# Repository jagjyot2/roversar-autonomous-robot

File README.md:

# RoverSAR — Autonomous Search & Rescue Ground Robot

**RoverSAR** is an autonomous differential-drive search-and-rescue (SAR) ground robot combining modular **PlatformIO ESP32 C++ firmware**, a **FastAPI + WebSocket 2D physics/SLAM simulator**, a **responsive React + TypeScript dark-mode control HUD**, **3D-printable OpenSCAD/STL chassis CAD**, **KiCad 8 schematics & BOM**, and a **BenchTwin** hardware staging package.

---

## Key Capabilities

- **Modular ESP32 Firmware (`firmware/`)**:
  - `motor_control/`: Differential-drive inverse/forward kinematics, `50 Hz` anti-windup wheel encoder PID, `20 kHz` TB6612FNG / L298N PWM driver.
  - `sensors/`: 5-channel `VL53L0X` ToF array (`XSHUT` address reassignment `0x30..0x34`), `MPU6050` IMU yaw/tilt fusion, `IRAM_ATTR` quadrature encoder odometry (`1440 CPR`), ADC1 2S Li-Ion battery monitor.
  - `navigation/`: 2D Bayesian log-odds occupancy grid mapper + VFH+ local reactive obstacle avoidance + waypoint pursuit.
  - `safety/`: Deterministic **500 ms comm-loss heartbeat watchdog** (immediate motor halt), IMU `> 35°` rollover cutoff, critical battery cutoff (`<= 6.0 V`), and latched software/hardware NC E-STOP.
  - `communication/` & `camera/`: Built-in RFC-6455 WebSocket + HTTP JSON server and ESP32-CAM MJPEG stream link.
- **2D Physics Simulator & Responsive Control HUD (`simulator/` + `dashboard/`)**:
  - Real-time `50 Hz` differential-drive dynamics, ToF laser raycasting against indoor SAR rooms/debris, live occupancy grid SLAM, and synthetic raycasted FPV ESP32-CAM JPEG/MJPEG stream.
  - Dark-mode React + TypeScript HUD served directly at `/` featuring a **touch virtual joystick + WASD**, **live 2D occupancy map & laser rays canvas**, **click-to-set-waypoint**, **FPV camera HUD**, **RPM/battery/watchdog gauges**, **E-STOP**, and **"Simulate Comm Loss (500ms Test)"** fault injection.
- **Mechanical CAD, KiCad & BenchTwin (`cad/`, `hardware/`, `benchtwin/`)**:
  - `240 × 180 × 95 mm` PETG chassis deck (`roversar_base_plate.stl`), 5-beam ToF sensor arc (`vl53l0x_sensor_mount.stl`), and 15° ESP32-CAM tilt bracket (`esp32_cam_tilt_bracket.stl`).
  - Complete KiCad 8 schematic, netlist, `BOM.csv`, mechanical/CG analysis, GPIO wiring map, and BenchTwin staging package.

---

## Quick Start

### 1. Run Simulator & Web Control HUD
```bash
pip install -r requirements.txt
uvicorn simulator.rover_sim_server:app --host 0.0.0.0 --port 8050
```
Open **`http://localhost:8050`** on desktop or mobile:
- Use **WASD / Arrow keys** or the **virtual touch joystick** to drive manually.
- **Click/tap anywhere** inside the 2D arena map to dispatch an autonomous VFH+ waypoint.
- Click **"Simulate Comm Loss (500ms Test)"** to verify the watchdog trips `COMM_LOSS_500MS` and halts both motors within 500 ms.
- Click **EMERGENCY E-STOP** to immediately lock drive actuation.

### 2. Run Automated Verification Tests
```bash
pytest -v
```

### 3. Build ESP32 Firmware (`firmware/`) & Run Wokwi Simulation (`wokwi/`)
```bash
cd firmware
pio run
```
Once built, `wokwi/wokwi.toml` points directly to `firmware/.pio/build/esp32dev/firmware.bin` and `firmware.elf`.
- **VS Code Wokwi Extension**: Open `wokwi/diagram.json` and run **Wokwi: Start Simulator**.
- **Wokwi CLI**: Set `WOKWI_CLI_TOKEN` and run `wokwi-cli` inside `wokwi/` (see [`wokwi/README.md`](./wokwi/README.md)).
- **Supported vs. Stubbed Components**: `ESP32-WROOM-32D`, `MPU6050`, `HC-SR04`, `NC E-STOP`, `2S VBAT divider`, and PWM/fault LEDs are natively modeled in Wokwi; the 5-ch `VL53L0X` array, `TB6612FNG` + 1440 CPR quadrature encoders, and `ESP32-CAM` use custom Wokwi chip stubs paired with the 50 Hz Python physics harness (see [`simulation/documentation/COMPONENT-SUPPORT-MATRIX.md`](./simulation/documentation/COMPONENT-SUPPORT-MATRIX.md)).

### 4. Rebuild React + TypeScript Dashboard (`dashboard/`)
```bash
cd dashboard
npm install
npm run build
```

---

## Repository Structure
- `firmware/` — Modular PlatformIO ESP32 C++ project (`include/`, `src/`, `platformio.ini`)
- `simulator/` — FastAPI + WebSocket `/ws/rover` physics, raycasting, SLAM, VFH+, and safety engine
- `dashboard/` — React + TypeScript + Vite responsive dark-mode ground control UI (`dist/` served at `/`)
- `cad/` — OpenSCAD `.scad` sources, reproducible STL builder, and binary `.stl` meshes
- `hardware/` — `CHASSIS-DESIGN.md`, `WIRING-DIAGRAM.md`, `roversar.kicad_sch`, `roversar.net`, `BOM.csv`
- `simulation/` — Simulator-independent HAL (`adapters/common/`), active `wokwi/` adapter, preserved `benchtwin/` manifest, fault/navigation `scenarios/`, and `COMPONENT-SUPPORT-MATRIX.md`
- `wokwi/` — Active Wokwi ESP32 diagram (`diagram.json`), `wokwi.toml`, and custom chip stubs (`chip-quad-encoder`, `chip-vl53l0x-array`)
- `benchtwin/` — Preserved BenchTwin hardware-in-the-loop staging package (`roversar.btw`, manifest, netlist, BOM, STL) for future reactivation
- `tests/` — Automated pytest suite covering kinematics, PID, odometry/mapping, wall avoidance, 500 ms failsafe, FastAPI/WS, STL, KiCad & BenchTwin validation
- `docs/ARCHITECTURE.md` & `ROADMAP.md` — System architecture & future engineering roadmap

---

## License
Released under the [MIT License](./LICENSE).

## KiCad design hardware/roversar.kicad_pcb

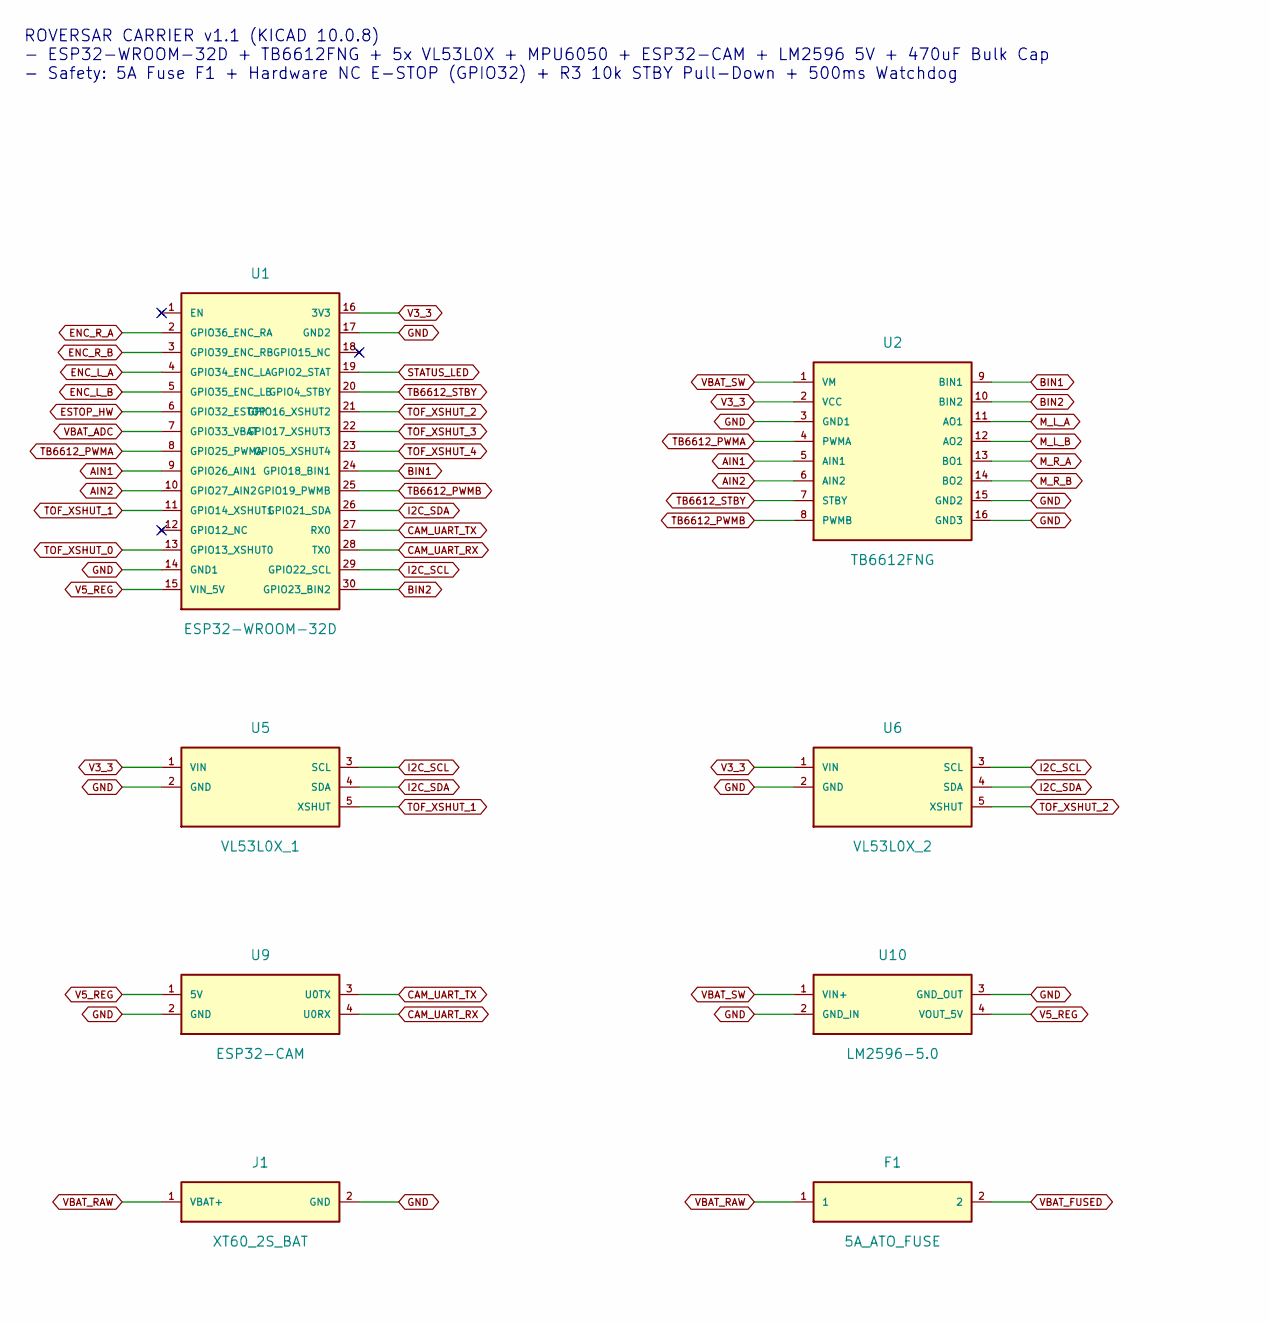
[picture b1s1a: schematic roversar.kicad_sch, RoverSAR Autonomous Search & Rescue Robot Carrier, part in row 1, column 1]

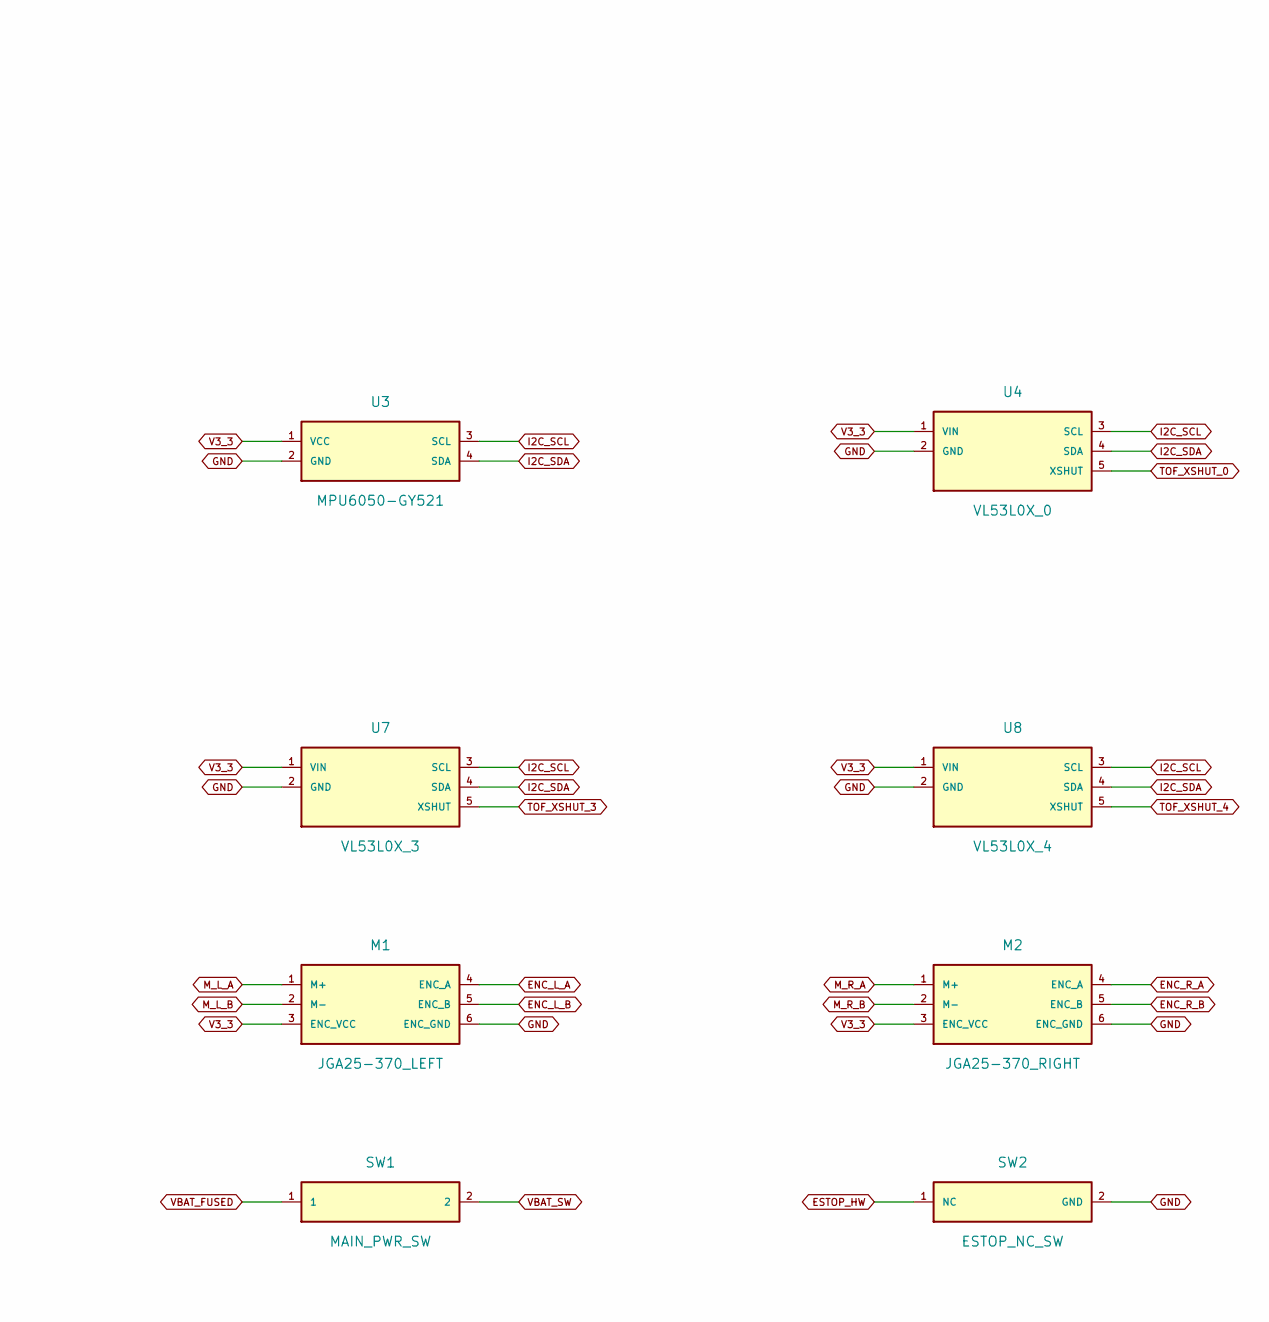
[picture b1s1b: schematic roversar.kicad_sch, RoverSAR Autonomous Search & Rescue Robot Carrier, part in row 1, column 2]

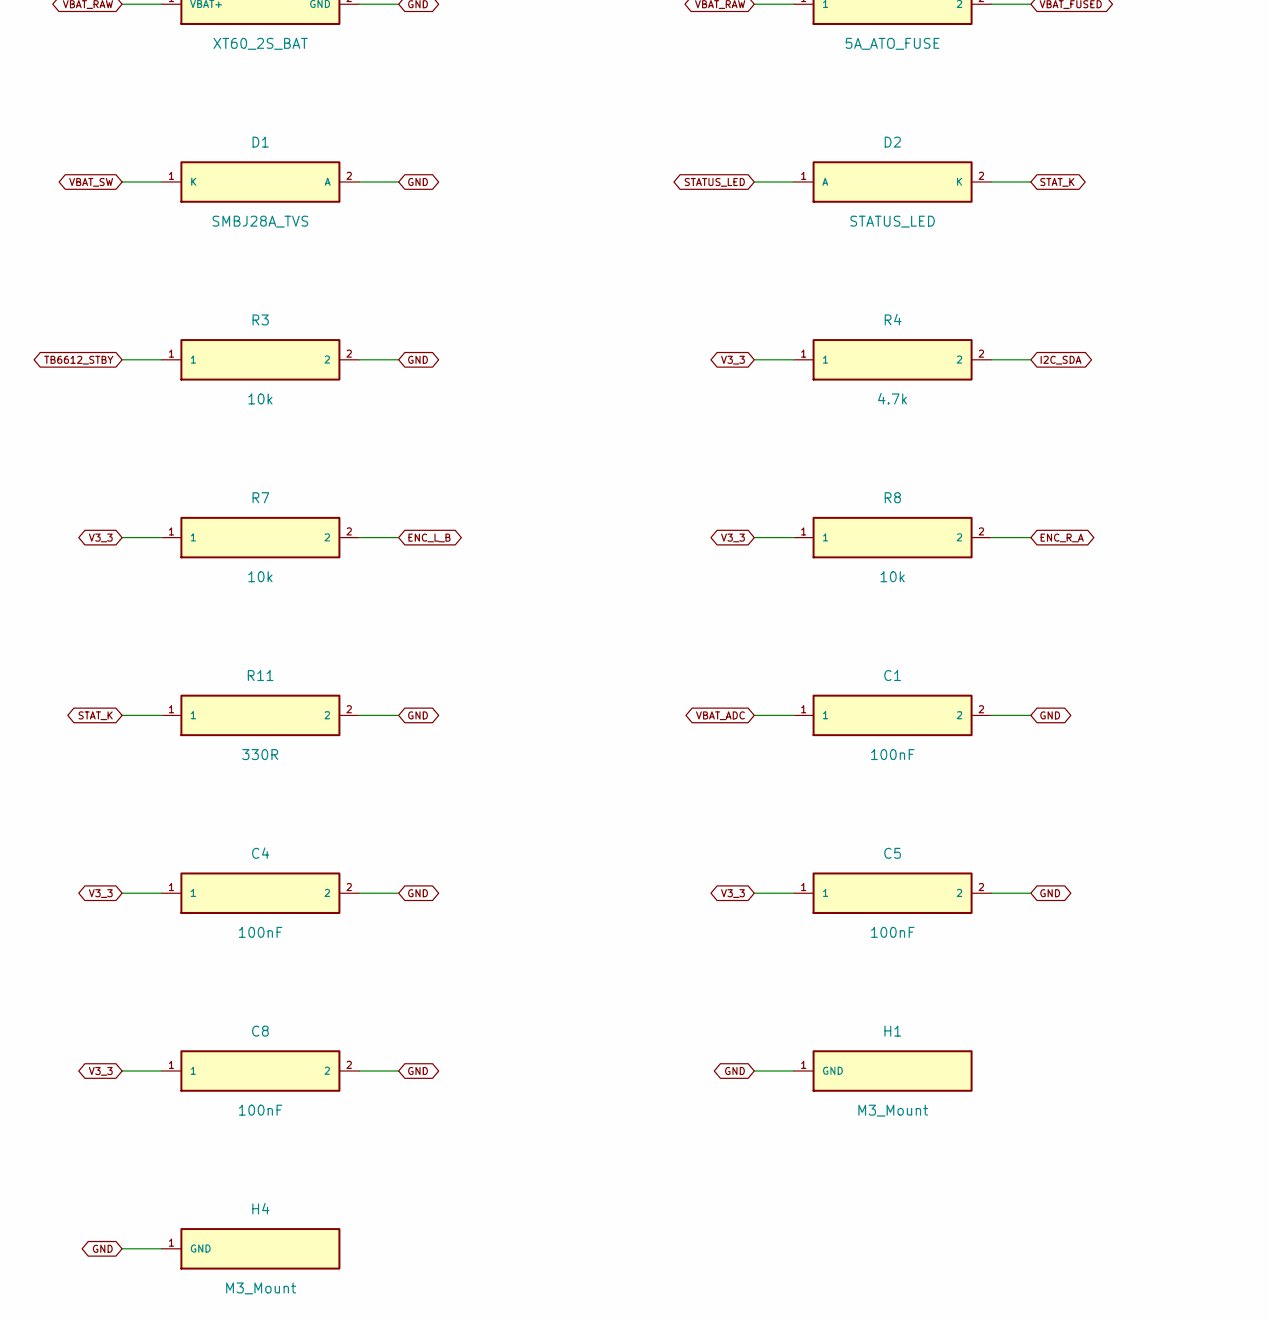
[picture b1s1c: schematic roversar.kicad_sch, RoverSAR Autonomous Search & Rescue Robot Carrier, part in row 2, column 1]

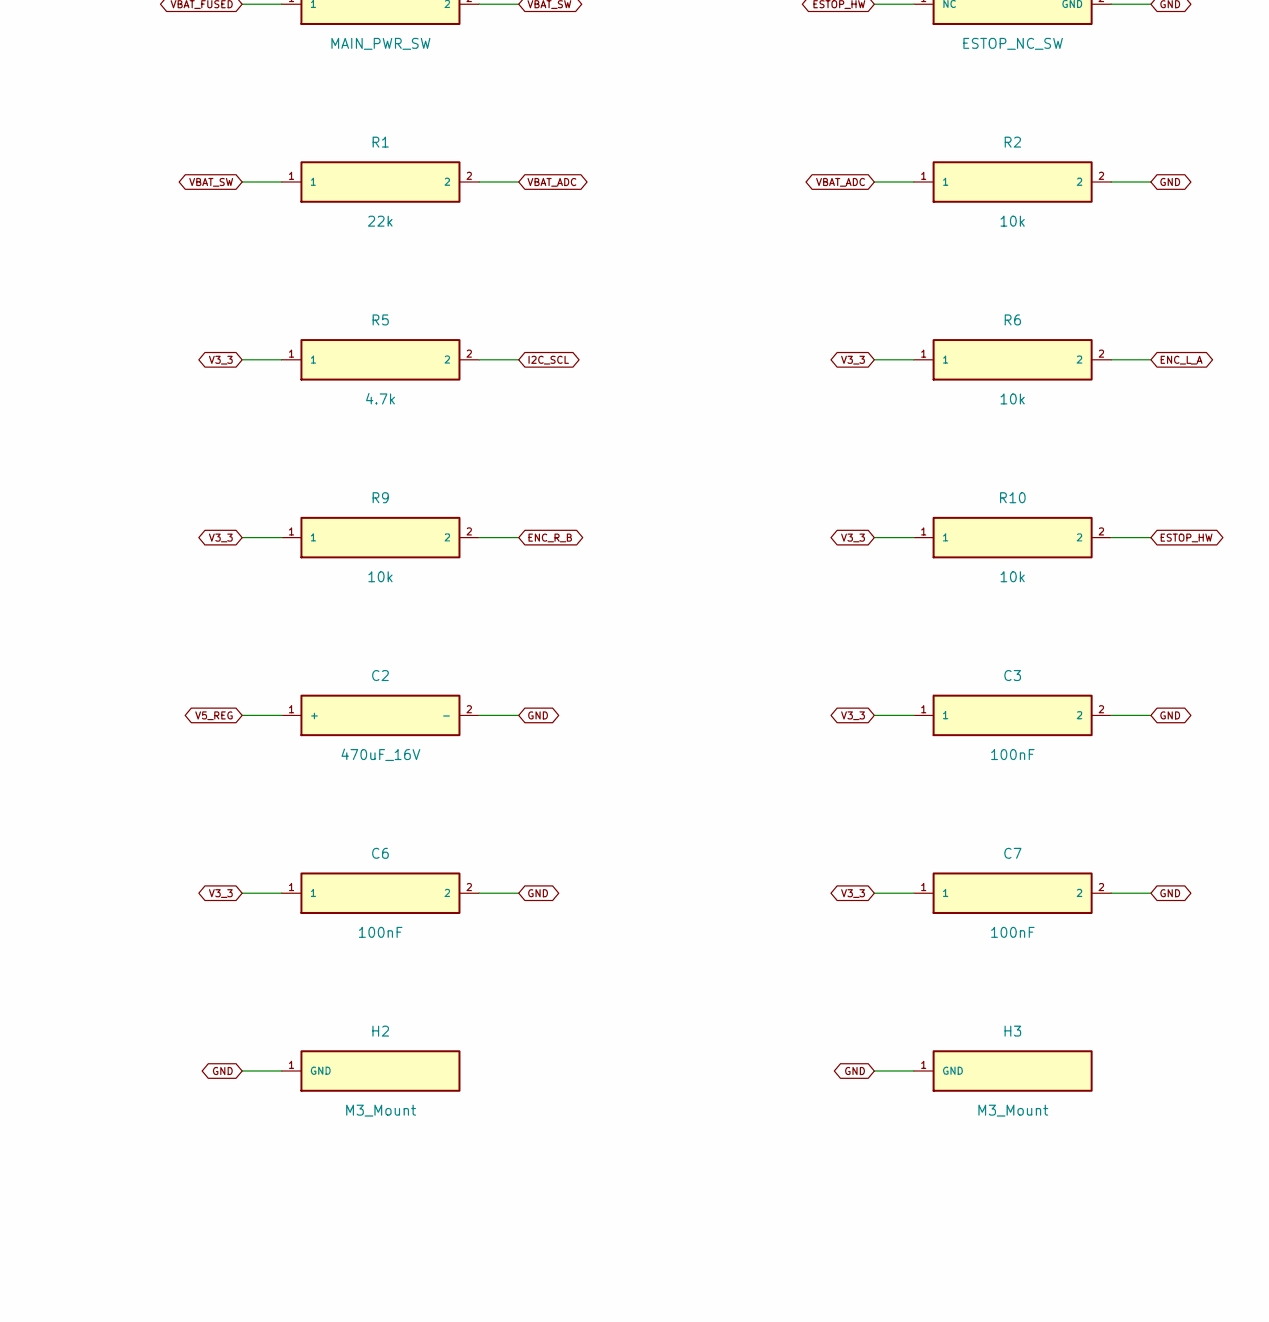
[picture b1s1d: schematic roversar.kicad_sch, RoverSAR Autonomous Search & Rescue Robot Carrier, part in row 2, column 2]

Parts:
C1: 100nF; SMD_0805; Rating 50V
C2: 470uF_16V; CP_Radial_D8mm; Rating 16V / 470uF
C3, C4, C5, C6, C7, C8: 100nF; SMD_0805; Rating 25V
D1: SMBJ28A_TVS; D_SMB; Rating 28V / 600W; MPN SMBJ28A
D2: STATUS_LED; SMD_0805; Rating 2.1V / 20mA; MPN LED-0805
F1: 5A_ATO_FUSE; Fuseholder_Blade_ATO_Littelfuse_Pudenz_2_Pin; Rating 32V / 5A ATO; MPN 0287005
H1, H2, H3, H4: M3_Mount; MountingHole_3.2mm_M3_Pad_Via; Rating M3
J1: XT60_2S_BAT; AMASS_XT60_Vertical; Rating 2S 7.4V / 30A; MPN XT60-M
M1: JGA25-370_LEFT; JST_XH_B6B-XH-A_1x06_P2.50mm_Vertical; Rating 7.4V / 1.5A; MPN JGA25-370
M2: JGA25-370_RIGHT; JST_XH_B6B-XH-A_1x06_P2.50mm_Vertical; Rating 7.4V / 1.5A; MPN JGA25-370
R1: 22k; SMD_0805; Rating 50V / 0.125W
R2, R3, R6, R7, R8, R9, R10: 10k; SMD_0805; Rating 50V / 0.125W
R4, R5: 4.7k; SMD_0805; Rating 50V / 0.125W
R11: 330R; SMD_0805; Rating 50V / 0.125W
SW1: MAIN_PWR_SW; TerminalBlock_bornier-2_P5.08mm; Rating 10A / 5.08mm; MPN R13-112 / TB-5.08
SW2: ESTOP_NC_SW; PinHeader_1x02_P2.54mm; Rating 3.3V Logic; MPN ESTOP-16MM
U1: ESP32-WROOM-32D; ESP32_DevKit_30P; Rating 3.3V IO / 5V VIN; MPN ESP32-DevKitC-32D
U2: TB6612FNG; Breakout_16Pin_DIP; Rating 15V / 1.2A cont (3.2A peak); MPN TB6612FNG
U3: MPU6050-GY521; JST_XH_B4B-XH-A_1x04_P2.50mm_Vertical; Rating 3.3V / I2C 0x68; MPN GY-521
U4: VL53L0X_0; JST_XH_B5B-XH-A_1x05_P2.50mm_Vertical; Rating 3.3V / I2C; MPN GY-530
U5: VL53L0X_1; JST_XH_B5B-XH-A_1x05_P2.50mm_Vertical; Rating 3.3V / I2C; MPN GY-530
U6: VL53L0X_2; JST_XH_B5B-XH-A_1x05_P2.50mm_Vertical; Rating 3.3V / I2C; MPN GY-530
U7: VL53L0X_3; JST_XH_B5B-XH-A_1x05_P2.50mm_Vertical; Rating 3.3V / I2C; MPN GY-530
U8: VL53L0X_4; JST_XH_B5B-XH-A_1x05_P2.50mm_Vertical; Rating 3.3V / I2C; MPN GY-530
U9: ESP32-CAM; JST_XH_B4B-XH-A_1x04_P2.50mm_Vertical; Rating 5.0V / 500mA + UART; MPN ESP32-CAM
U10: LM2596-5.0; Buck_4Pin_Module; Rating 7-35V -> 5V / 3A; MPN LM2596SX-5.0

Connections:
AIN1: U1.9 (GPIO26_AIN1), U2.5 (AIN1)
AIN2: U1.10 (GPIO27_AIN2), U2.6 (AIN2)
BIN1: U1.24 (GPIO18_BIN1), U2.9 (BIN1)
BIN2: U1.30 (GPIO23_BIN2), U2.10 (BIN2)
CAM_UART_RX: U1.28 (TX0), U9.4 (U0RX)
CAM_UART_TX: U1.27 (RX0), U9.3 (U0TX)
ENC_L_A: M1.4 (ENC_A), R6.2, U1.4 (GPIO34_ENC_LA)
ENC_L_B: M1.5 (ENC_B), R7.2, U1.5 (GPIO35_ENC_LB)
ENC_R_A: M2.4 (ENC_A), R8.2, U1.2 (GPIO36_ENC_RA)
ENC_R_B: M2.5 (ENC_B), R9.2, U1.3 (GPIO39_ENC_RB)
ESTOP_HW: R10.2, SW2.1 (NC), U1.6 (GPIO32_ESTOP)
GND: C1.2, C2.2 (-), C3.2, C4.2, C5.2, C6.2, C7.2, C8.2, D1.2 (A), H1.1, H2.1, H3.1, H4.1, J1.2 (GND), M1.6 (ENC_GND), M2.6 (ENC_GND), R2.2, R3.2, R11.2, SW2.2 (GND), U1.14 (GND1), U1.17 (GND2), U2.3 (GND1), U2.15 (GND2), U2.16 (GND3), U3.2 (GND), U4.2 (GND), U5.2 (GND), U6.2 (GND), U7.2 (GND), U8.2 (GND), U9.2 (GND), U10.2 (GND_IN), U10.3 (GND_OUT)
I2C_SCL: R5.2, U1.29 (GPIO22_SCL), U3.3 (SCL), U4.3 (SCL), U5.3 (SCL), U6.3 (SCL), U7.3 (SCL), U8.3 (SCL)
I2C_SDA: R4.2, U1.26 (GPIO21_SDA), U3.4 (SDA), U4.4 (SDA), U5.4 (SDA), U6.4 (SDA), U7.4 (SDA), U8.4 (SDA)
M_L_A: M1.1 (M+), U2.11 (AO1)
M_L_B: M1.2 (M-), U2.12 (AO2)
M_R_A: M2.1 (M+), U2.13 (BO1)
M_R_B: M2.2 (M-), U2.14 (BO2)
STATUS_LED: D2.1 (A), U1.19 (GPIO2_STAT)
STAT_K: D2.2 (K), R11.1
TB6612_PWMA: U1.8 (GPIO25_PWMA), U2.4 (PWMA)
TB6612_PWMB: U1.25 (GPIO19_PWMB), U2.8 (PWMB)
TB6612_STBY: R3.1, U1.20 (GPIO4_STBY), U2.7 (STBY)
TOF_XSHUT_0: U1.13 (GPIO13_XSHUT0), U4.5 (XSHUT)
TOF_XSHUT_1: U1.11 (GPIO14_XSHUT1), U5.5 (XSHUT)
TOF_XSHUT_2: U1.21 (GPIO16_XSHUT2), U6.5 (XSHUT)
TOF_XSHUT_3: U1.22 (GPIO17_XSHUT3), U7.5 (XSHUT)
TOF_XSHUT_4: U1.23 (GPIO5_XSHUT4), U8.5 (XSHUT)
V3_3: C3.1, C4.1, C5.1, C6.1, C7.1, C8.1, M1.3 (ENC_VCC), M2.3 (ENC_VCC), R4.1, R5.1, R6.1, R7.1, R8.1, R9.1, R10.1, U1.16 (3V3), U2.2 (VCC), U3.1 (VCC), U4.1 (VIN), U5.1 (VIN), U6.1 (VIN), U7.1 (VIN), U8.1 (VIN)
V5_REG: C2.1 (+), U1.15 (VIN_5V), U9.1 (5V), U10.4 (VOUT_5V)
VBAT_ADC: C1.1, R1.2, R2.1, U1.7 (GPIO33_VBAT)
VBAT_FUSED: F1.2, SW1.1
VBAT_RAW: F1.1, J1.1 (VBAT+)
VBAT_SW: D1.1 (K), R1.1, SW1.2, U2.1 (VM), U10.1 (VIN+)

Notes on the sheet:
ROVERSAR CARRIER v1.1 (KICAD 10.0.8) - ESP32-WROOM-32D + TB6612FNG + 5x VL53L0X + MPU6050 + ESP32-CAM + LM2596 5V + 470uF Bulk Cap - Safety: 5A Fuse F1 + Hardware NC E-STOP (GPIO32) + R3 10k STBY Pull-Down + 500ms Watchdog

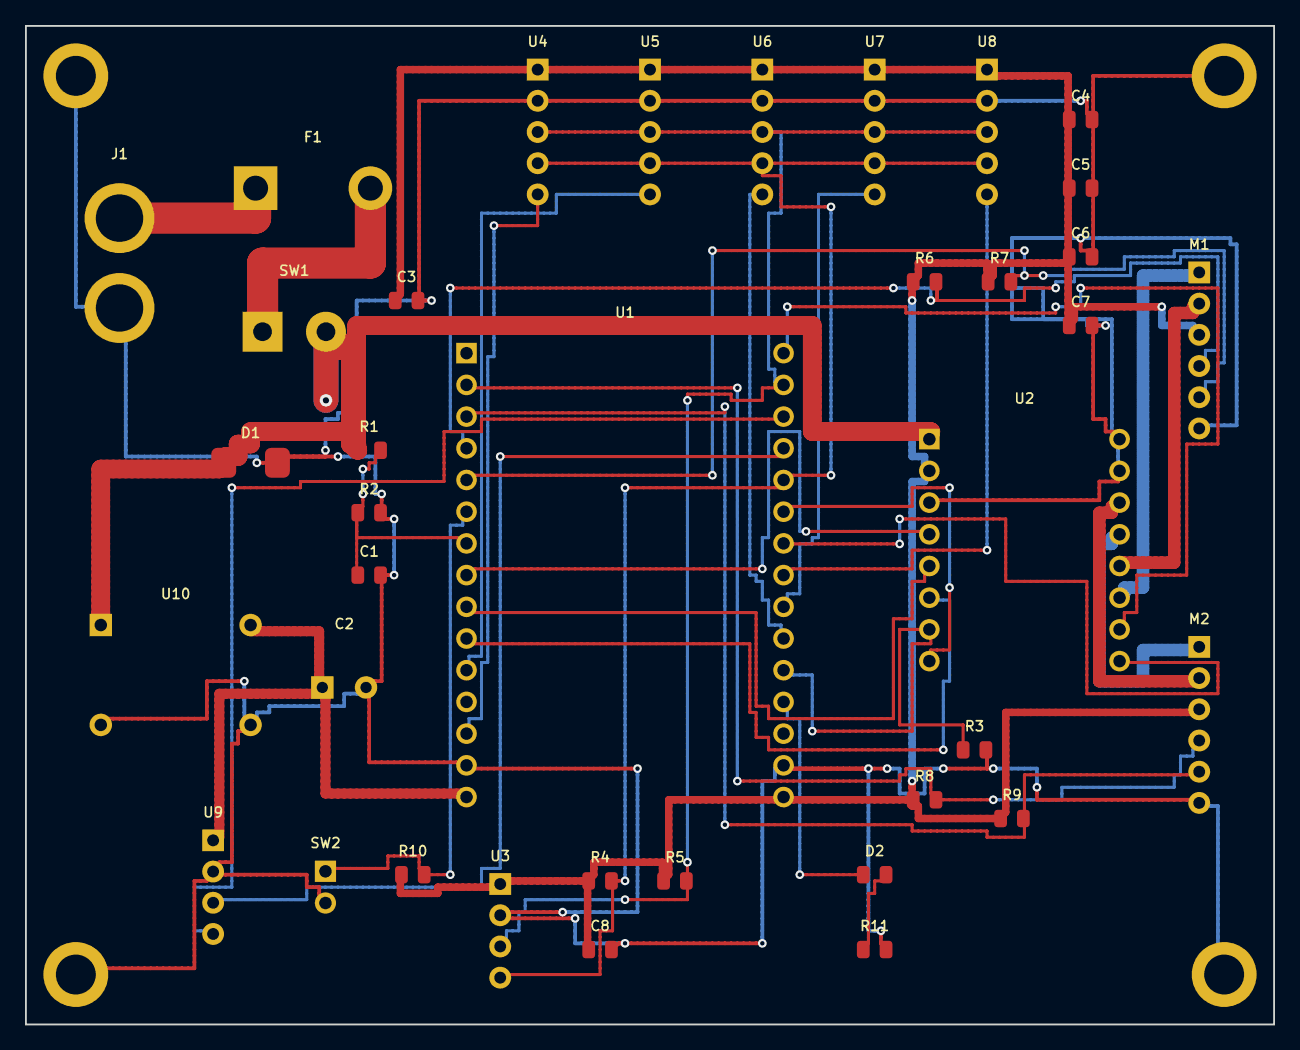
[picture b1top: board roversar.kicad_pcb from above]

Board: 2 copper layers, 100.0 x 80.0 mm, 41 parts (0 on the bottom side), 34 nets.

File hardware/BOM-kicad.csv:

"Designator","Value","Footprint","MPN","Manufacturer","Rating","Qty"
"C1","100nF","RoverSAR:SMD_0805","","","50V","1"
"C2","470uF_16V","RoverSAR:CP_Radial_D8mm","","","16V / 470uF","1"
"C3","100nF","RoverSAR:SMD_0805","","","25V","1"
"C4","100nF","RoverSAR:SMD_0805","","","25V","1"
"C5","100nF","RoverSAR:SMD_0805","","","25V","1"
"C6","100nF","RoverSAR:SMD_0805","","","25V","1"
"C7","100nF","RoverSAR:SMD_0805","","","25V","1"
"C8","100nF","RoverSAR:SMD_0805","","","25V","1"
"D1","SMBJ28A_TVS","RoverSAR:D_SMB","SMBJ28A","","28V / 600W","1"
"D2","STATUS_LED","RoverSAR:SMD_0805","LED-0805","","2.1V / 20mA","1"
"F1","5A_ATO_FUSE","RoverSAR:Fuseholder_Blade_ATO_Littelfuse_Pudenz_2_Pin","0287005","","32V / 5A ATO","1"
"H1","M3_Mount","RoverSAR:MountingHole_3.2mm_M3_Pad_Via","","","M3","1"
"H2","M3_Mount","RoverSAR:MountingHole_3.2mm_M3_Pad_Via","","","M3","1"
"H3","M3_Mount","RoverSAR:MountingHole_3.2mm_M3_Pad_Via","","","M3","1"
"H4","M3_Mount","RoverSAR:MountingHole_3.2mm_M3_Pad_Via","","","M3","1"
"J1","XT60_2S_BAT","RoverSAR:AMASS_XT60_Vertical","XT60-M","","2S 7.4V / 30A","1"
"M1","JGA25-370_LEFT","RoverSAR:JST_XH_B6B-XH-A_1x06_P2.50mm_Vertical","JGA25-370","Generic","7.4V / 1.5A","1"
"M2","JGA25-370_RIGHT","RoverSAR:JST_XH_B6B-XH-A_1x06_P2.50mm_Vertical","JGA25-370","Generic","7.4V / 1.5A","1"
"R1","22k","RoverSAR:SMD_0805","","","50V / 0.125W","1"
"R2","10k","RoverSAR:SMD_0805","","","50V / 0.125W","1"
"R3","10k","RoverSAR:SMD_0805","","","50V / 0.125W","1"
"R4","4.7k","RoverSAR:SMD_0805","","","50V / 0.125W","1"
"R5","4.7k","RoverSAR:SMD_0805","","","50V / 0.125W","1"
"R6","10k","RoverSAR:SMD_0805","","","50V / 0.125W","1"
"R7","10k","RoverSAR:SMD_0805","","","50V / 0.125W","1"
"R8","10k","RoverSAR:SMD_0805","","","50V / 0.125W","1"
"R9","10k","RoverSAR:SMD_0805","","","50V / 0.125W","1"
"R10","10k","RoverSAR:SMD_0805","","","50V / 0.125W","1"
"R11","330R","RoverSAR:SMD_0805","","","50V / 0.125W","1"
"SW1","MAIN_PWR_SW","RoverSAR:TerminalBlock_bornier-2_P5.08mm","R13-112 / TB-5.08","","10A / 5.08mm","1"
"SW2","ESTOP_NC_SW","RoverSAR:PinHeader_1x02_P2.54mm","ESTOP-16MM","","3.3V Logic","1"
"U1","ESP32-WROOM-32D","RoverSAR:ESP32_DevKit_30P","ESP32-DevKitC-32D","Espressif","3.3V IO / 5V VIN","1"
"U2","TB6612FNG","RoverSAR:Breakout_16Pin_DIP","TB6612FNG","Toshiba / Pololu","15V / 1.2A cont (3.2A peak)","1"
"U3","MPU6050-GY521","RoverSAR:JST_XH_B4B-XH-A_1x04_P2.50mm_Vertical","GY-521","InvenSense","3.3V / I2C 0x68","1"
"U4","VL53L0X_0","RoverSAR:JST_XH_B5B-XH-A_1x05_P2.50mm_Vertical","GY-530","STMicroelectronics","3.3V / I2C","1"
"U5","VL53L0X_1","RoverSAR:JST_XH_B5B-XH-A_1x05_P2.50mm_Vertical","GY-530","STMicroelectronics","3.3V / I2C","1"
"U6","VL53L0X_2","RoverSAR:JST_XH_B5B-XH-A_1x05_P2.50mm_Vertical","GY-530","STMicroelectronics","3.3V / I2C","1"
"U7","VL53L0X_3","RoverSAR:JST_XH_B5B-XH-A_1x05_P2.50mm_Vertical","GY-530","STMicroelectronics","3.3V / I2C","1"
"U8","VL53L0X_4","RoverSAR:JST_XH_B5B-XH-A_1x05_P2.50mm_Vertical","GY-530","STMicroelectronics","3.3V / I2C","1"
"U9","ESP32-CAM","RoverSAR:JST_XH_B4B-XH-A_1x04_P2.50mm_Vertical","ESP32-CAM","Ai-Thinker","5.0V / 500mA + UART","1"
"U10","LM2596-5.0","RoverSAR:Buck_4Pin_Module","LM2596SX-5.0","TI","7-35V -> 5V / 3A","1"

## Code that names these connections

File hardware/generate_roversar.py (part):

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            f"{LIB}:ESP32_DevKit_30P",
            [
                kt.SchPin("1", "EN", "NC_EN", "left", "no_connect"),
                kt.SchPin("2", "GPIO36_ENC_RA", "ENC_R_A", "left"),
                kt.SchPin("3", "GPIO39_ENC_RB", "ENC_R_B", "left"),
                kt.SchPin("4", "GPIO34_ENC_LA", "ENC_L_A", "left"),
                kt.SchPin("5", "GPIO35_ENC_LB", "ENC_L_B", "left"),
                kt.SchPin("6", "GPIO32_ESTOP", "ESTOP_HW", "left"),
                kt.SchPin("7", "GPIO33_VBAT", "VBAT_ADC", "left"),
                kt.SchPin("8", "GPIO25_PWMA", "TB6612_PWMA", "left"),
                kt.SchPin("9", "GPIO26_AIN1", "AIN1", "left"),
                kt.SchPin("10", "GPIO27_AIN2", "AIN2", "left"),
                kt.SchPin("11", "GPIO14_XSHUT1", "TOF_XSHUT_1", "left"),
                kt.SchPin("12", "GPIO12_NC", "NC_D12", "left", "no_connect"),
                kt.SchPin("13", "GPIO13_XSHUT0", "TOF_XSHUT_0", "left"),
                kt.SchPin("14", "GND1", "GND", "left"),
                kt.SchPin("15", "VIN_5V", "V5_REG", "left"),
                kt.SchPin("16", "3V3", "V3_3", "right"),
                kt.SchPin("17", "GND2", "GND", "right"),
                kt.SchPin("18", "GPIO15_NC", "NC_D15", "right", "no_connect"),
                kt.SchPin("19", "GPIO2_STAT", "STATUS_LED", "right"),
                kt.SchPin("20", "GPIO4_STBY", "TB6612_STBY", "right"),
                kt.SchPin("21", "GPIO16_XSHUT2", "TOF_XSHUT_2", "right"),
                kt.SchPin("22", "GPIO17_XSHUT3", "TOF_XSHUT_3", "right"),
                kt.SchPin("23", "GPIO5_XSHUT4", "TOF_XSHUT_4", "right"),
                kt.SchPin("24", "GPIO18_BIN1", "BIN1", "right"),
                kt.SchPin("25", "GPIO19_PWMB", "TB6612_PWMB", "right"),
                kt.SchPin("26", "GPIO21_SDA", "I2C_SDA", "right"),
                kt.SchPin("27", "RX0", "CAM_UART_TX", "right"),
                kt.SchPin("28", "TX0", "CAM_UART_RX", "right"),
                kt.SchPin("29", "GPIO22_SCL", "I2C_SCL", "right"),
                kt.SchPin("30", "GPIO23_BIN2", "BIN2", "right"),
            ],
            mpn="ESP32-DevKitC-32D",
            manufacturer="Espressif",
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            "TB6612FNG",
            f"{LIB}:Breakout_16Pin_DIP",
            [
                kt.SchPin("1", "VM", "VBAT_SW", "left"),
                kt.SchPin("2", "VCC", "V3_3", "left"),
                kt.SchPin("3", "GND1", "GND", "left"),
                kt.SchPin("4", "PWMA", "TB6612_PWMA", "left"),
                kt.SchPin("5", "AIN1", "AIN1", "left"),
                kt.SchPin("6", "AIN2", "AIN2", "left"),
                kt.SchPin("7", "STBY", "TB6612_STBY", "left"),
                kt.SchPin("8", "PWMB", "TB6612_PWMB", "left"),
                kt.SchPin("9", "BIN1", "BIN1", "right"),
                kt.SchPin("10", "BIN2", "BIN2", "right"),
                kt.SchPin("11", "AO1", "M_L_A", "right"),
                kt.SchPin("12", "AO2", "M_L_B", "right"),
                kt.SchPin("13", "BO1", "M_R_A", "right"),
                kt.SchPin("14", "BO2", "M_R_B", "right"),
                kt.SchPin("15", "GND2", "GND", "right"),
                kt.SchPin("16", "GND3", "GND", "right"),
            ],
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            "MPU6050-GY521",
            f"{LIB}:JST_XH_B4B-XH-A_1x04_P2.50mm_Vertical",
            [
                kt.SchPin("1", "VCC", "V3_3", "left"),
                kt.SchPin("2", "GND", "GND", "left"),
                kt.SchPin("3", "SCL", "I2C_SCL", "right"),
                kt.SchPin("4", "SDA", "I2C_SDA", "right"),
            ],
            mpn="GY-521",
            manufacturer="InvenSense",
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                f"VL53L0X_{idx}",
                f"{LIB}:JST_XH_B5B-XH-A_1x05_P2.50mm_Vertical",
                [
                    kt.SchPin("1", "VIN", "V3_3", "left"),
                    kt.SchPin("2", "GND", "GND", "left"),
                    kt.SchPin("3", "SCL", "I2C_SCL", "right"),
                    kt.SchPin("4", "SDA", "I2C_SDA", "right"),
                    kt.SchPin("5", "XSHUT", f"TOF_XSHUT_{idx}", "right"),
                ],
                mpn="GY-530",
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            "ESP32-CAM",
            f"{LIB}:JST_XH_B4B-XH-A_1x04_P2.50mm_Vertical",
            [
                kt.SchPin("1", "5V", "V5_REG", "left"),
                kt.SchPin("2", "GND", "GND", "left"),
                kt.SchPin("3", "U0TX", "CAM_UART_TX", "right"),
                kt.SchPin("4", "U0RX", "CAM_UART_RX", "right"),
            ],
            mpn="ESP32-CAM",
            manufacturer="Ai-Thinker",
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            "LM2596-5.0",
            f"{LIB}:Buck_4Pin_Module",
            [
                kt.SchPin("1", "VIN+", "VBAT_SW", "left"),
                kt.SchPin("2", "GND_IN", "GND", "left"),
                kt.SchPin("3", "GND_OUT", "GND", "right"),
                kt.SchPin("4", "VOUT_5V", "V5_REG", "right"),
            ],
            mpn="LM2596SX-5.0",
            manufacturer="TI",
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            "JGA25-370_LEFT",
            f"{LIB}:JST_XH_B6B-XH-A_1x06_P2.50mm_Vertical",
            [
                kt.SchPin("1", "M+", "M_L_A", "left"),
                kt.SchPin("2", "M-", "M_L_B", "left"),
                kt.SchPin("3", "ENC_VCC", "V3_3", "left"),
                kt.SchPin("4", "ENC_A", "ENC_L_A", "right"),
                kt.SchPin("5", "ENC_B", "ENC_L_B", "right"),
                kt.SchPin("6", "ENC_GND", "GND", "right"),
            ],
            mpn="JGA25-370",
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            "JGA25-370_RIGHT",
            f"{LIB}:JST_XH_B6B-XH-A_1x06_P2.50mm_Vertical",
            [
                kt.SchPin("1", "M+", "M_R_A", "left"),
                kt.SchPin("2", "M-", "M_R_B", "left"),
                kt.SchPin("3", "ENC_VCC", "V3_3", "left"),
                kt.SchPin("4", "ENC_A", "ENC_R_A", "right"),
                kt.SchPin("5", "ENC_B", "ENC_R_B", "right"),
                kt.SchPin("6", "ENC_GND", "GND", "right"),
            ],
            mpn="JGA25-370",
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    )

    # Battery, ATO Blade Fuse (9.2mm pitch), Main Switch Terminal (5.08mm pitch), TVS, E-STOP
    sb.add_component(kt.SchComponent("J1", "XT60_2S_BAT", f"{LIB}:AMASS_XT60_Vertical", [kt.SchPin("1", "VBAT+", "VBAT_RAW", "left"), kt.SchPin("2", "GND", "GND", "right")], mpn="XT60-M", rating="2S 7.4V / 30A"))
    sb.add_component(kt.SchComponent("F1", "5A_ATO_FUSE", f"{LIB}:Fuseholder_Blade_ATO_Littelfuse_Pudenz_2_Pin", [kt.SchPin("1", "1", "VBAT_RAW", "left"), kt.SchPin("2", "2", "VBAT_FUSED", "right")], mpn="0287005", rating="32V / 5A ATO"))
    sb.add_component(kt.SchComponent("SW1", "MAIN_PWR_SW", f"{LIB}:TerminalBlock_bornier-2_P5.08mm", [kt.SchPin("1", "1", "VBAT_FUSED", "left"), kt.SchPin("2", "2", "VBAT_SW", "right")], mpn="R13-112 / TB-5.08", rating="10A / 5.08mm"))
    sb.add_component(kt.SchComponent("SW2", "ESTOP_NC_SW", f"{LIB}:PinHeader_1x02_P2.54mm", [kt.SchPin("1", "NC", "ESTOP_HW", "left"), kt.SchPin("2", "GND", "GND", "right")], mpn="ESTOP-16MM", rating="3.3V Logic"))
    sb.add_component(kt.SchComponent("D1", "SMBJ28A_TVS", f"{LIB}:D_SMB", [kt.SchPin("1", "K", "VBAT_SW", "left"), kt.SchPin("2", "A", "GND", "right")], mpn="SMBJ28A", rating="28V / 600W"))
    sb.add_component(kt.SchComponent("D2", "STATUS_LED", f"{LIB}:SMD_0805", [kt.SchPin("1", "A", "STATUS_LED", "left"), kt.SchPin("2", "K", "STAT_K", "right")], mpn="LED-0805", rating="2.1V / 20mA"))

    # Resistors & Caps
    res = [
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    for ref, val, n1, n2 in res:
        sb.add_component(kt.SchComponent(ref, val, f"{LIB}:SMD_0805", [kt.SchPin("1", "1", n1, "left"), kt.SchPin("2", "2", n2, "right")], rating="50V / 0.125W"))

    sb.add_component(kt.SchComponent("C1", "100nF", f"{LIB}:SMD_0805", [kt.SchPin("1", "1", "VBAT_ADC", "left"), kt.SchPin("2", "2", "GND", "right")], rating="50V"))
    sb.add_component(kt.SchComponent("C2", "470uF_16V", f"{LIB}:CP_Radial_D8mm", [kt.SchPin("1", "+", "V5_REG", "left"), kt.SchPin("2", "-", "GND", "right")], rating="16V / 470uF"))
    for idx in range(3, 9):
        sb.add_component(kt.SchComponent(f"C{idx}", "100nF", f"{LIB}:SMD_0805", [kt.SchPin("1", "1", "V3_3", "left"), kt.SchPin("2", "2", "GND", "right")], rating="25V"))

    for h in ("H1", "H2", "H3", "H4"):
        sb.add_component(kt.SchComponent(h, "M3_Mount", f"{LIB}:MountingHole_3.2mm_M3_Pad_Via", [kt.SchPin("1", "GND", "GND", "left")], rating="M3"))
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

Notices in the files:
README.md:
License: MIT
